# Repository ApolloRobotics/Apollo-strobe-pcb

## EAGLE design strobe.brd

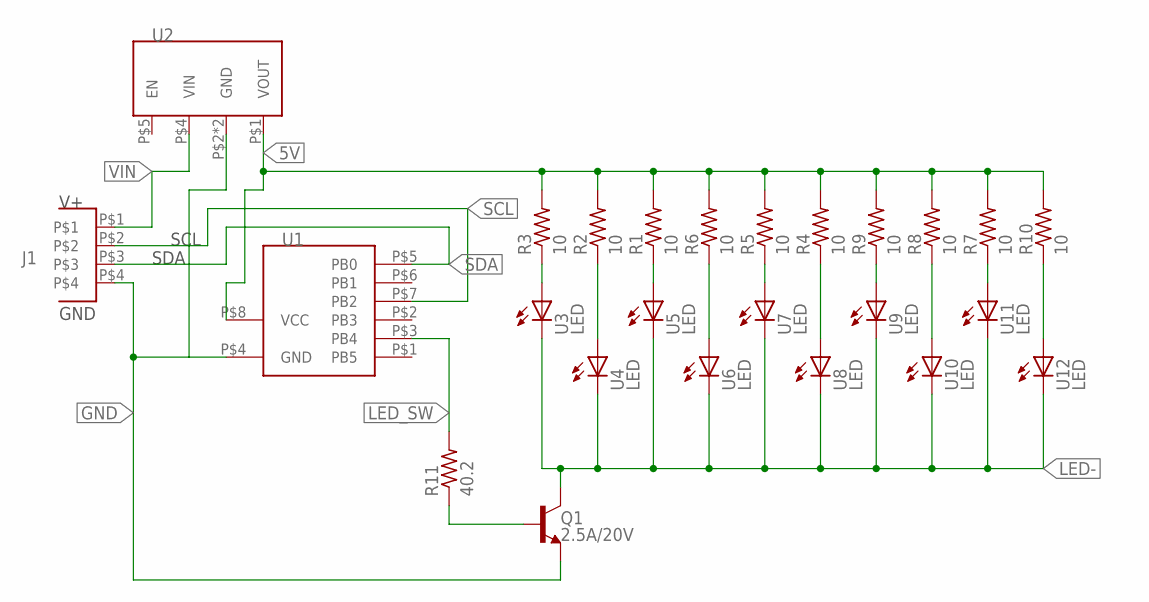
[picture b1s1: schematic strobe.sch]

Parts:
J1: MOLEX-04365004; MOLEX-43650-04
Q1: 2.5A/20V; SOT23-3
R1, R2, R3, R4, R5, R6, R7, R8, R9, R10: 10; R0805
R11: 40.2; R0805
U1: ATTINY85; 8P3
U2: D24V25F5
U3, U4, U5, U6, U7, U8, U9, U10, U11, U12: LED; 3030

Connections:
5V: R1.2, R2.2, R3.2, R4.2, R5.2, R6.2, R7.2, R8.2, R9.2, R10.2, U1.P$8 (VCC), U2.P$1 (VOUT)
GND: J1.P$4, Q1.2 (E), U1.P$4 (GND), U2.P$2 (GND), U2.P$3 (GND)
LED-: Q1.3 (C), U3.CATH (C), U4.CATH (C), U5.CATH (C), U6.CATH (C), U7.CATH (C), U8.CATH (C), U9.CATH (C), U10.CATH (C), U11.CATH (C), U12.CATH (C)
LED_SW: R11.2, U1.P$3 (PB4)
unnamed: R3.1, U3.ANODE (A)
unnamed: R1.1, U5.ANODE (A)
unnamed: R6.1, U6.ANODE (A)
unnamed: R5.1, U7.ANODE (A)
unnamed: R4.1, U8.ANODE (A)
unnamed: R9.1, U9.ANODE (A)
unnamed: R8.1, U10.ANODE (A)
unnamed: R7.1, U11.ANODE (A)
unnamed: R10.1, U12.ANODE (A)
unnamed: Q1.1 (B), R11.1
SCL: J1.P$2, U1.P$7 (PB2)
SDA: J1.P$3, U1.P$5 (PB0)
U$: R2.1, U4.ANODE (A)
VIN: J1.P$1, U2.P$4 (VIN)

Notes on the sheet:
GND
SDA
SCL

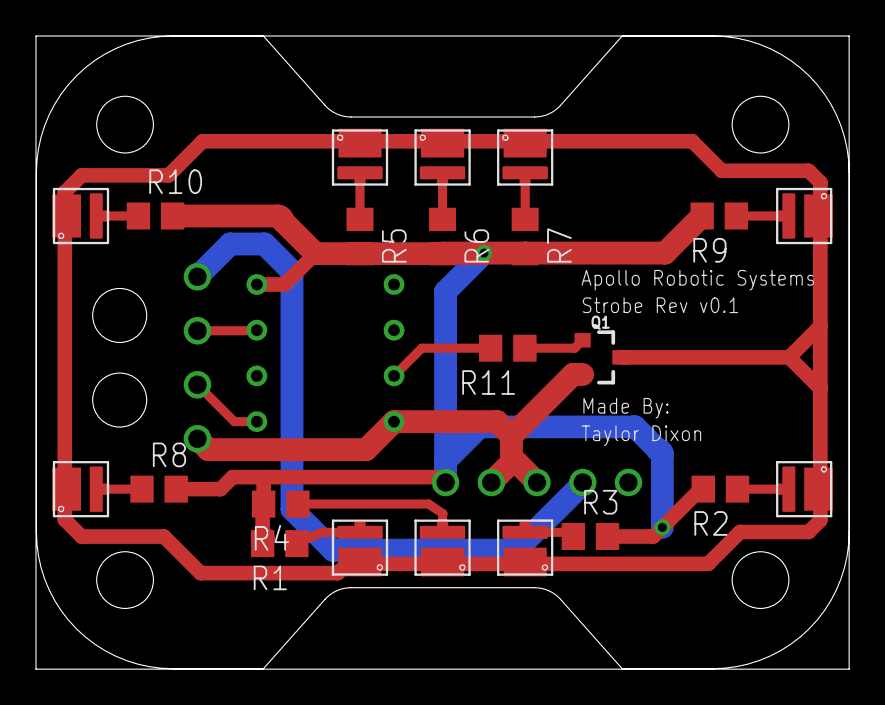
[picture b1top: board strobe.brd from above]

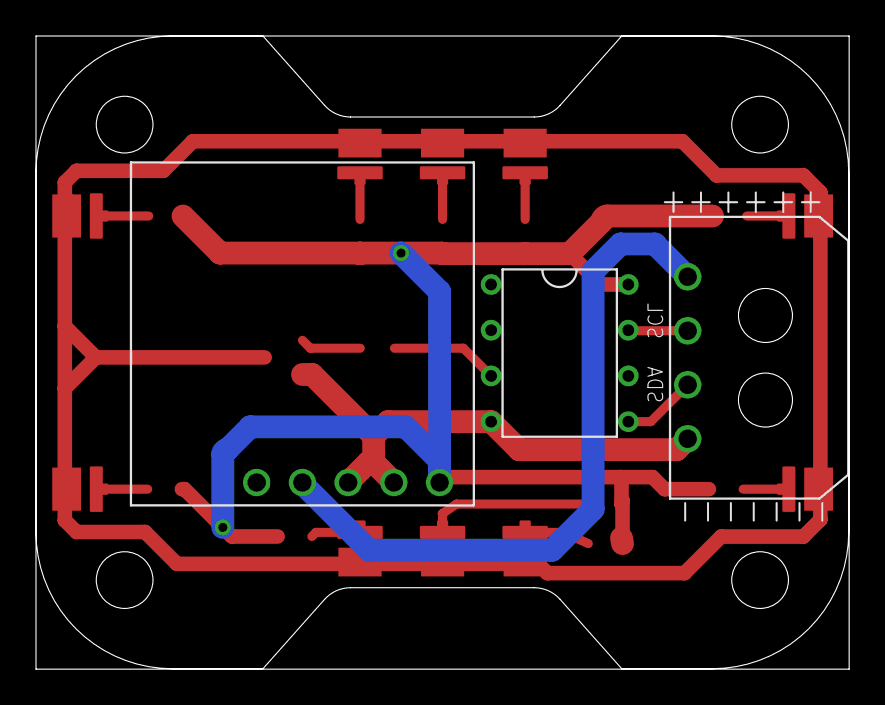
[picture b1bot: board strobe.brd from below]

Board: 2 copper layers, 45.2 x 35.2 mm, 25 parts (3 on the bottom side), 18 nets.

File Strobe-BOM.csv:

,Apollo Robotic Systems - Strobe - BOM,,,,,,
,Rev v0.1,,,,,,
Item #,Ref Des,Qty,Manufacturer,Mfg Part #,Description / Value,Package,Type
1,"U3, U4, U5, U6, U7, U8, U9, U10, U11, U12",10,Luminus Devices Inc.,MP-3030-1100-57-70, LED MID PWR 5700K 70CRI,L3030,SMD
2,Q1,1,Diodes Incorporated,ZXT11N20DFTA,TRANS NPN 20V 2.5A ,SOT23-3,SMD
3,"R1, R2, R3, R4, R5, R6, R7, R8, R9, R10",10,Panasonic Electronic Components,ERJ-P6WF10R0V,RES SMD 10 OHM 1% 1/2W,R0805,SMD
4,R11,1,Panasonic Electronic Components,ERJ-P06F40R2V,RES SMD 40.2 OHM 1% 1/2W,R0805,SMD

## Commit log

2018-06-29 first
2019-01-15 current version post print

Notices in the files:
parts and their libraries:
SparkFun-DiscreteSemi: Licensing: Creative Commons ShareAlike 4.0 International - https://creativecommons.org/licenses/by-sa/4.0
